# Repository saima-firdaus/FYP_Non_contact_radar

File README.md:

# FYP Non-contact radar
Ive been using the jremington library for the DWM1000 ESP32 UWB Makerfabs radar.
https://github.com/jremington/UWB-Indoor-Localization_Arduino 

Ive modified it to work with my NLOS project and it is effectively giving me the CIR accumulator plots needed. To give you some context I am trying to modify the jremington library so I can plot the CIR accumulator graph and see the different peaks, my goal is to see the peak corresponding to a reflection off a human. Phase 0 will just use those Makerfabs modules however Phase 1 will do hardware upgrades. My goal is to compare the CIR graphs using many different signal processing methods (like filtering and averaging) for both phases and show that Phase 1 improved upon phase 0.

Currently I am testing different environmental setups like:

tag - anchor (unobstructed LOS) - (To see if the direct peak is the strongest or not, which it should be).

tag-anchor (with obstruction) - To see if the direct LOS peak is weak or not. (it should be)

tag-anchor (with obstruction and/or human standing to the side) - This is to see if there is a secondary peak coming off that human on the CIR graph.

Your goal is to use this information for understanding purposes, I have questions and am working on improvements. 

This is the GitHUB repo I am working on: https://github.com/saima-firdaus/FYP_Non_contact_radar. Im working off the old_version_BMDA branch.

I am a slow learner so I prefer simplicity and in depth explanations rather than heavy jargon, so please use this to frame your answers.

I am basing the software algorithms off the paper found here:
https://www.researchgate.net/publication/376302345_Impact_of_CIR_processing_for_UWB_radar_distance_estimation_with_the_DW1000_transceiver 

You can see the current software algorithm in use in the CIR_capture.m file and then the CIR_phase_analysis.m file.

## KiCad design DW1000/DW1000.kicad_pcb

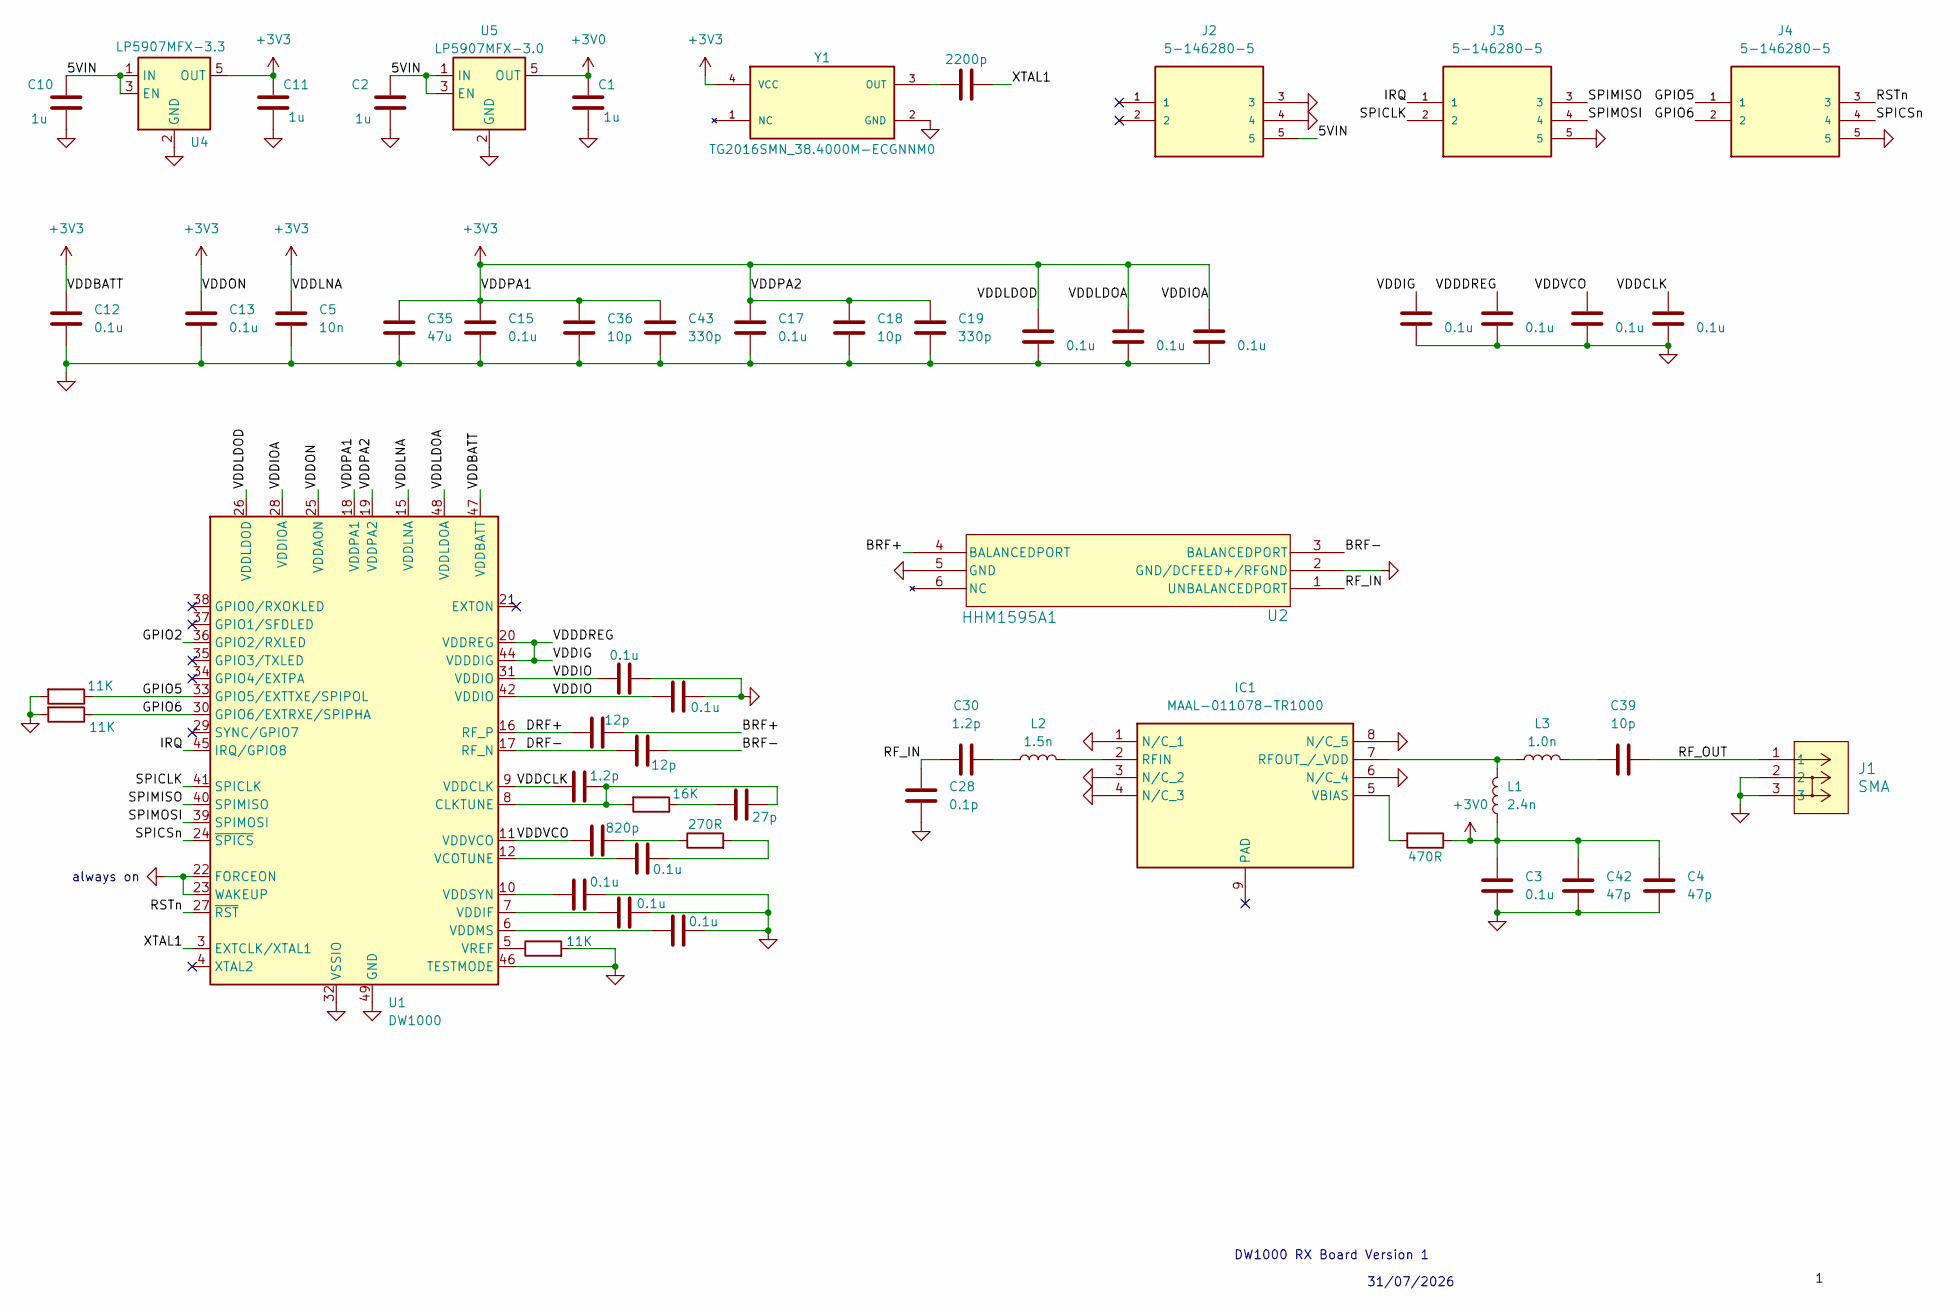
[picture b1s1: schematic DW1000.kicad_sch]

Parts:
C1, C2, C10, C11: 1u; C_0402_1005Metric
C3, C12, C13, C15, C16, C17, C20, C21, C22, C23, C24, C25, C26, C27, C29, C31, C40, C41: 0.1u; C_0402_1005Metric
C4, C42: 47p; C_0402_1005Metric
C5: 10n; C_0402_1005Metric
C7, C9: 12p; C_0402_1005Metric
C18, C36, C39: 10p; C_0402_1005Metric
C19, C43: 330p; C_0402_1005Metric
C28: 0.1p; C_0402_1005Metric
C30, C34: 1.2p; C_0402_1005Metric
C32: 820p; C_0402_1005Metric
C33: 27p; C_0402_1005Metric
C35: 47u; C_0402_1005Metric
C37: 2200p; C_0402_1005Metric
IC1: MAAL-011078-TR1000; SON50P200X200X100-9N; Mouser Part Number 937-MAAL-011078T1
J1: SMA; CONN_SMA-J-P-H-ST-EM1_SAI
J2, J3, J4: 5-146280-5; TE_5-146280-5; PARTREV R
L1: 2.4n; L_0402_1005Metric
L2: 1.5n; L_0402_1005Metric
L3: 1.0n; L_0402_1005Metric
R1, R2, R3: 11K; R_0402_1005Metric
R4: 16K; R_0402_1005Metric
R5: 270R; R_0402_1005Metric
R6: 470R; R_0402_1005Metric
U1: DW1000; QFN-48-1EP_6x6mm_P0.4mm_EP4.2x4.2mm
U2: HHM1595A1; HHM-6_2P0X1P25
U4: LP5907MFX-3.3; SOT-23-5
U5: LP5907MFX-3.0; SOT-23-5
Y1: TG2016SMN_38.4000M-ECGNNM0; OSC_TG2016SMN_38.4000M-ECGNNM0; PARTREV 1.3

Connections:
+3V0: C1.1, C3.1, C4.1, C42.1, L1.1, R6.1, U5.5 (OUT)
+3V3: C5.1, C11.1, C12.1, C13.1, C15.1, C16.1, C17.1, C18.1, C19.1, C20.1, C29.1, C35.1, C36.1, C43.1, U1.15 (VDDLNA), U1.18 (VDDPA1), U1.19 (VDDPA2), U1.25 (VDDAON), U1.26 (VDDLDOD), U1.28 (VDDIOA), U1.47 (VDDBATT), U1.48 (VDDLDOA), U4.5 (OUT), Y1.4 (VCC)
/5VIN: C2.1, C10.1, J2.5, U4.1 (IN), U4.3 (EN), U5.1 (IN), U5.3 (EN)
/BRF+: C7.2, U2.4 (BALANCEDPORT)
/BRF-: C9.2, U2.3 (BALANCEDPORT)
/DRF+: C7.1, U1.16 (RF_P)
/DRF-: C9.1, U1.17 (RF_N)
/GPIO2: U1.36 (GPIO2/RXLED)
/GPIO5: J4.1, R1.1, U1.33 (GPIO5/EXTTXE/SPIPOL)
/GPIO6: J4.2, R2.1, U1.30 (GPIO6/EXTRXE/SPIPHA)
/IRQ: J3.1, U1.45 (IRQ/GPIO8)
/RF_IN: C28.1, C30.1, U2.1 (UNBALANCEDPORT)
/RF_OUT: C39.2, J1.1
/RSTn: J4.3, U1.27 (~RST)
/SPICLK: J3.2, U1.41 (SPICLK)
/SPICSn: J4.4, U1.24 (~SPICS)
/SPIMISO: J3.3, U1.40 (SPIMISO)
/SPIMOSI: J3.4, U1.39 (SPIMOSI)
/VDDCLK: C27.1, C34.2, U1.9 (VDDCLK)
/VDDDREG: C22.1, C23.1, U1.20 (VDDREG), U1.44 (VDDDIG)
/VDDIO: C40.1, C41.1, U1.31 (VDDIO), U1.42 (VDDIO)
/VDDVCO: C26.1, C32.1, U1.11 (VDDVCO)
/XTAL1: C37.2, U1.3 (EXTCLK/XTAL1)
GND: C1.2, C2.2, C3.2, C4.2, C5.2, C10.2, C11.2, C12.2, C13.2, C15.2, C16.2, C17.2, C18.2, C19.2, C20.2, C21.2, C22.2, C23.2, C24.2, C25.2, C26.2, C27.2, C28.2, C29.2, C35.2, C36.2, C40.2, C41.2, C42.2, C43.2, IC1.1 (N/C_1), IC1.3 (N/C_2), IC1.4 (N/C_3), IC1.6 (N/C_4), IC1.8 (N/C_5), J1.2, J1.3, J2.3, J2.4, J3.5, J4.5, R1.2, R2.2, R3.2, U1.22 (FORCEON), U1.23 (WAKEUP), U1.32 (VSSIO), U1.43 (VSSIO), U1.46 (TESTMODE), U1.49 (GND), U2.2 (GND/DCFEED+/RFGND), U2.5 (GND), U4.2 (GND), U5.2 (GND), Y1.2 (GND)
unnamed: C30.2, L2.1
unnamed: C31.2, R5.2
unnamed: C32.2, R5.1
unnamed: C33.2, R4.1
unnamed: C39.1, L3.2
unnamed: IC1.2 (RFIN), L2.2
unnamed: IC1.7 (RFOUT_/_VDD), L1.2, L3.1
unnamed: IC1.5 (VBIAS), R6.2
unnamed: C33.1, C34.1, R4.2, U1.8 (CLKTUNE)
unnamed: C31.1, U1.12 (VCOTUNE)
unnamed: C24.1, U1.7 (VDDIF)
unnamed: C25.1, U1.6 (VDDMS)
unnamed: C21.1, U1.10 (VDDSYN)
unnamed: R3.1, U1.5 (VREF)
unnamed: C37.1, Y1.3 (OUT)

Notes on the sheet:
DW1000 RX Board Version 1
always on
31/07/2026

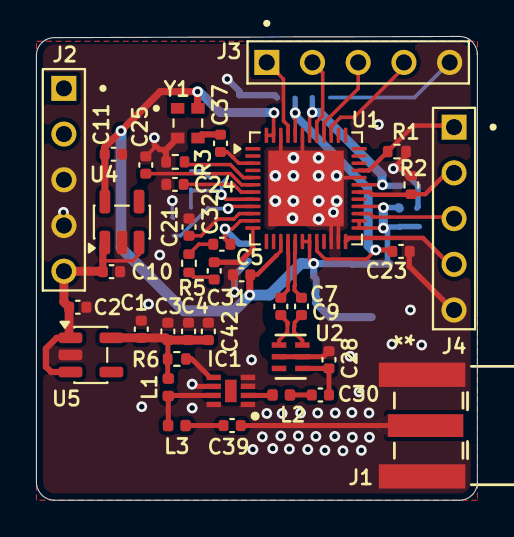
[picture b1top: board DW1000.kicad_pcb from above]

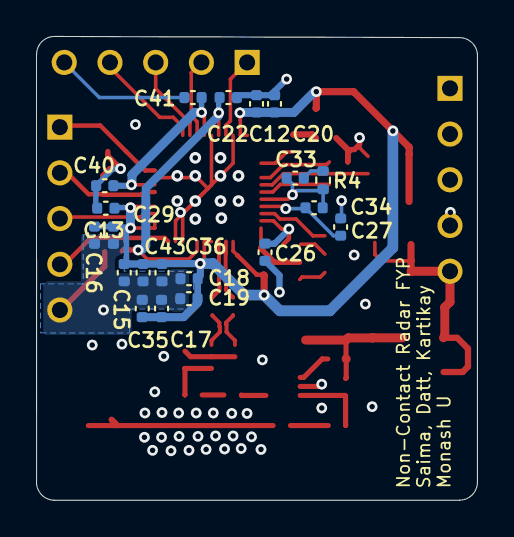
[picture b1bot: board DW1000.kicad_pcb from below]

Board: 4 copper layers, 24.5 x 25.8 mm, 58 parts (20 on the bottom side), 38 nets.

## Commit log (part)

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2026-05-28 Starting off PCB for Version 0
